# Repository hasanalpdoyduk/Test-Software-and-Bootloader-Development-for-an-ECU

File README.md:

# Test Software and Bootloader Development for an ECU

A bootloader has been developed that enables firmware updates without external programmers. The system runs on a 16-bit dsPIC33 microcontroller and supports CAN and UART interfaces.

Software is securely transferred via one of these interfaces and written to the microcontroller's memory using a block-based architecture that ensures data integrity during interrupts. To streamline the update process, a Python-based graphical user interface (GUI) was created for real-time control and monitoring.

Furthermore, a custom board containing the dsPIC33 MCU was designed and manufactured, successfully testing the bootloader and a PWM control implementation.
## Hardware Components

To initially load the bootloader onto the microcontroller or test the PWM control code, an external debugger is required. In this project, Microchip’s **PICkit 5** is used to program the dsPIC33 device.

| Type         | Component                                                        |
| ----------------- | ------------------------------------------------------------------ |
| Microcontroller | [dsPIC33](https://ww1.microchip.com/downloads/aemDocuments/documents/OTH/ProductDocuments/DataSheets/dsPIC33EVXXXGM00X-10X-Family-Data-Sheet-DS70005144H.pdf) |
| CAN Transceiver | [MCP2561](https://ww1.microchip.com/downloads/en/DeviceDoc/20005167C.pdf) |
| LDO              | [LF50](https://www.st.com/resource/en/datasheet/lfxx.pdf) |
| TVS Diode| [SMAJ36CA](https://www.vishay.com/docs/88390/smaj50a.pdf) |
| Schottky Diode| [SS8PH10HM3](https://www.vishay.com/docs/88989/ss8ph10.pdf) |

In addition to main components, other hardware parts such as resistors, capacitors, connectors, and oscillators are listed in the [Bill of Materials (BOM)](https://github.com/hasanalpdoyduk/Test-Software-and-Bootloader-Development-for-an-ECU/blob/main/KiCAD/ECU_SW_Control/Production_Files/BOM/ECU_SW_Control.csv).

## Block Diagram

The fully assembled PCB is shown here: [3D View of PCB](https://github.com/hasanalpdoyduk/Test-Software-and-Bootloader-Development-for-an-ECU/blob/main/Images/3D_view.pdf)

## Tools & Libraries

- KiCad: Used for schematic and PCB design.

- MATLAB Simulink Device Blocks for Microchip: Used to model and generate initial versions of embedded code.

- MPLAB X IDE: Used to compile and flash generated C code to the dsPIC33 MCU.

- Python (PyQt): Used for GUI development to support user interaction and test control.

## Supporting Sources

All technical details and explanations related to the project are available in the [project report](https://github.com/hasanalpdoyduk/Test-Software-and-Bootloader-Development-for-an-ECU/blob/main/Report_Presentation/EE402_Final_Report_AlpDoyduk_S025015_I%CC%87smailAkbas_S024094.pdf). For more in-depth insights or specific inquiries, feel free to reach out via GitHub or refer to the resources listed below.

- [MCC dsPIC33 Bootlader - Video Guide](https://www.youtube.com/watch?v=2LhW11LbNhY): A step-by-step YouTube tutorial demonstrating how to implement a bootloader for dsPIC33 using Microchip Code Configurator (MCC).

- [Microchip Bootloader Library for 16-bit Devices](https://www.microchip.com/en-us/software-library/dspic33-pic24-bootloader): Official documentation and downloadable libraries for implementing bootloaders on 16-bit dsPIC33/PIC24 microcontrollers.

- [16-bit Bootloader Using MCC - Online Course](https://mu.microchip.com/16-bit-bootloaders-using-mcc-device-side): A Microchip University course explaining how to develop a bootloader for dsPIC33 using MCC, covering both theory and practice.
## Authors

- [Hasan Alp Doyduk](https://www.github.com/hasanalpdoyduk)
- [Ismail Akbaş](https://www.github.com/ismailakbas)

Supervised by: Asst. Prof. Umut Başaran

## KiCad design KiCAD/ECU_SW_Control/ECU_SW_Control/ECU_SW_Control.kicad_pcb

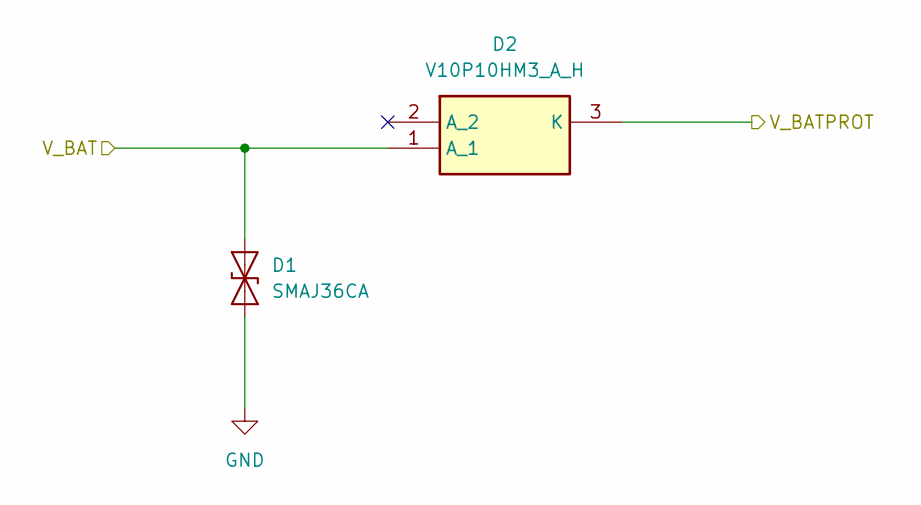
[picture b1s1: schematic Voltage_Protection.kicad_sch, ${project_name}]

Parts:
D1: SMAJ36CA; D_SMA
D2: V10P10HM3_A_H; TO-277A

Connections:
/Connector/V_BAT: D1.1 (A1), D2.1 (A_1); also elsewhere on the board
/LDO/V_BATPROT: D2.3 (K); also elsewhere on the board
GND: D1.2 (A2); also elsewhere on the board

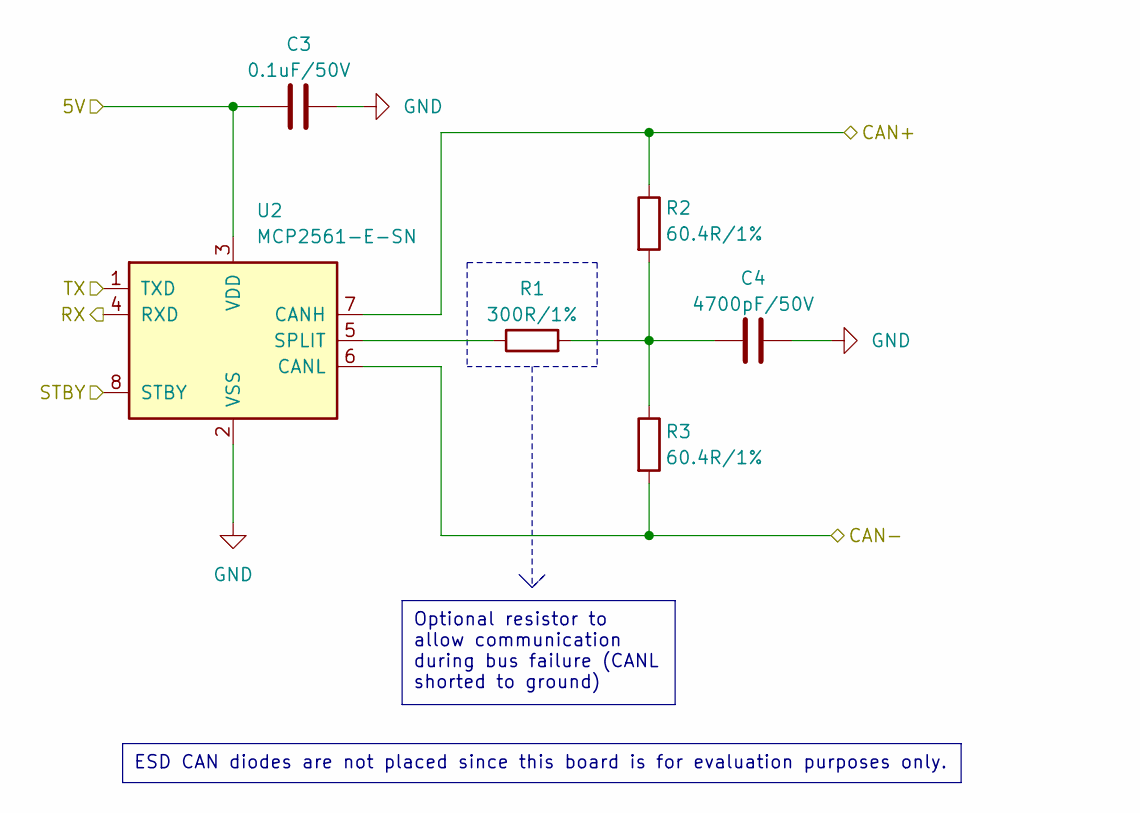
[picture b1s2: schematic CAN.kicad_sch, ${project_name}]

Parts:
C3: 0.1uF/50V; C_0603_1608Metric_Pad1.08x0.95mm_HandSolder; Voltage 50V; Part_Value 0.1uF
C4: 4700pF/50V; C_0603_1608Metric_Pad1.08x0.95mm_HandSolder; Voltage 50V; Part_Value 4700pF
R1: 300R/1%; R_0603_1608Metric_Pad0.98x0.95mm_HandSolder; Tolerance 1%; Part_Value 300R
R2, R3: 60.4R/1%; R_0603_1608Metric_Pad0.98x0.95mm_HandSolder; Tolerance 1%; Part_Value 60.4R
U2: MCP2561-E-SN; SOIC-8_3.9x4.9mm_P1.27mm

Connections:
/CAN/5V: C3.1, U2.3 (VDD); also elsewhere on the board
/CAN/CAN+: R2.1, U2.7 (CANH); also elsewhere on the board
/CAN/CAN-: R3.2, U2.6 (CANL); also elsewhere on the board
/CAN/RX: U2.4 (RXD); also elsewhere on the board
/CAN/STBY: U2.8 (STBY); also elsewhere on the board
/CAN/TX: U2.1 (TXD); also elsewhere on the board
GND: C3.2, C4.2, U2.2 (VSS); also elsewhere on the board
unnamed: C4.1, R1.2, R2.2, R3.1
unnamed: R1.1, U2.5 (SPLIT)

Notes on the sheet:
Optional resistor to allow communication during bus failure (CANL shorted to ground)
ESD CAN diodes are not placed since this board is for evaluation purposes only.

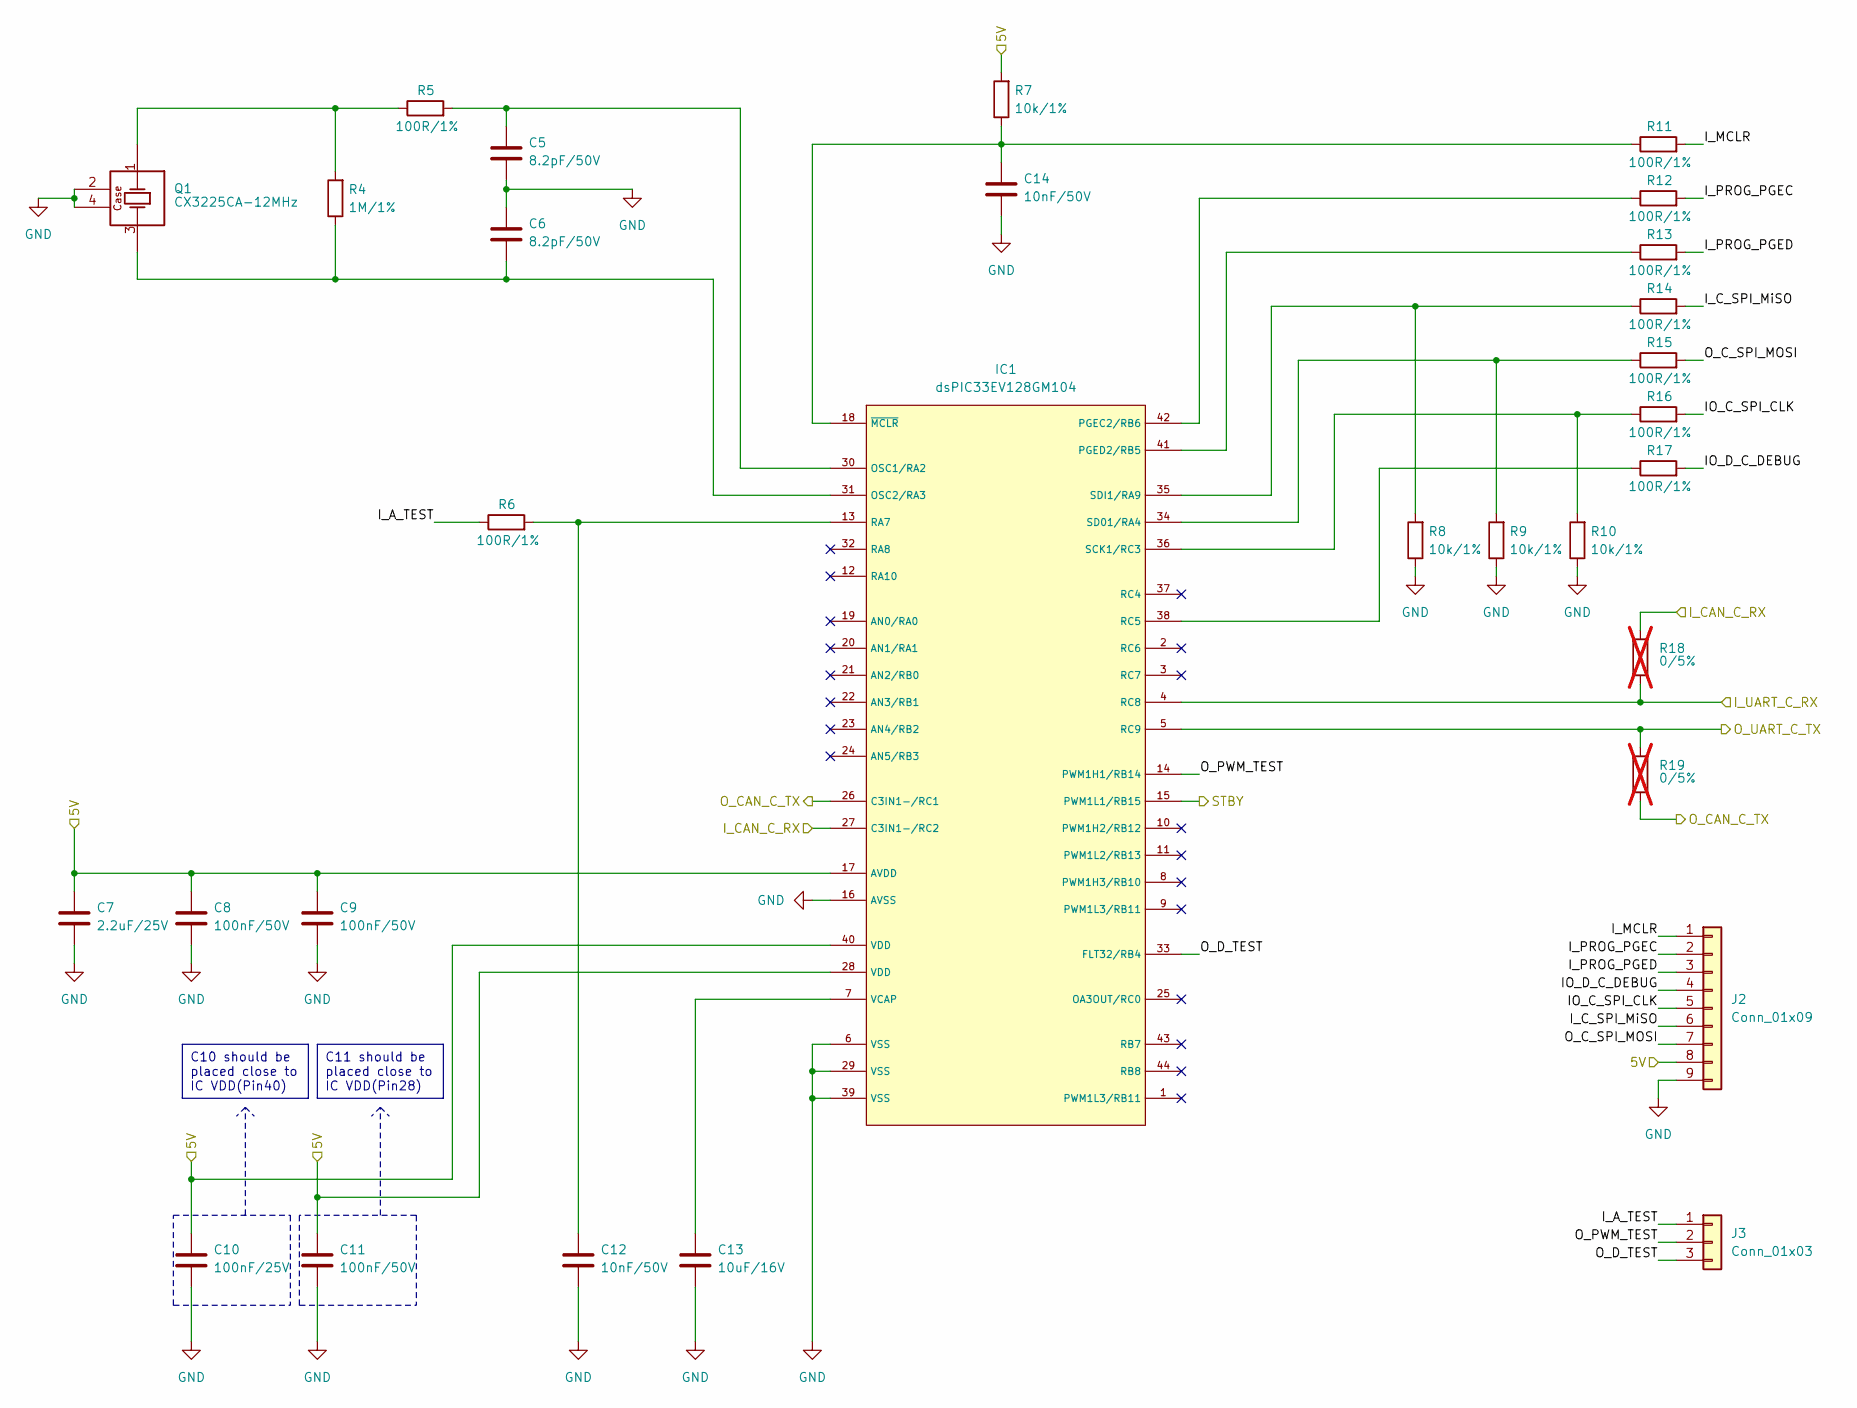
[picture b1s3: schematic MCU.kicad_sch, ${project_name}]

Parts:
C5, C6: 8.2pF/50V; C_0603_1608Metric_Pad1.08x0.95mm_HandSolder; Voltage 50V; Part_Value 8.2pF
C7: 2.2uF/25V; C_0603_1608Metric_Pad1.08x0.95mm_HandSolder; Voltage 25V; Part_Value 2.2uF
C8, C9, C11: 100nF/50V; C_0603_1608Metric_Pad1.08x0.95mm_HandSolder; Voltage 50V; Part_Value 100nF
C10: 100nF/25V; C_0603_1608Metric_Pad1.08x0.95mm_HandSolder; Voltage 25V; Part_Value 100nF
C12, C14: 10nF/50V; C_0603_1608Metric_Pad1.08x0.95mm_HandSolder; Voltage 50V; Part_Value 10nF
C13: 10uF/16V; C_0603_1608Metric_Pad1.08x0.95mm_HandSolder; Voltage 16V; Part_Value 10uF
IC1: dsPIC33EV128GM104; TQFP-44_10x10mm_P0.8mm
J2: Conn_01x09; PinHeader_1x09_P2.54mm_Vertical
J3: Conn_01x03; PinHeader_1x03_P2.54mm_Vertical
Q1: CX3225CA-12MHz; CX3225SB40000D0FLJCC
R4: 1M/1%; R_0603_1608Metric_Pad0.98x0.95mm_HandSolder; Tolerance 1%; Part_Value 1M
R5, R6, R11, R12, R13, R14, R15, R16, R17: 100R/1%; R_0603_1608Metric_Pad0.98x0.95mm_HandSolder; Tolerance 1%; Part_Value 100R
R7, R8, R9, R10: 10k/1%; R_0603_1608Metric_Pad0.98x0.95mm_HandSolder; Tolerance 1%; Part_Value 10k
R18, R19: 0/5%; R_0603_1608Metric_Pad0.98x0.95mm_HandSolder; Tolerance 5%; Part_Value 0; not fitted

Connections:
/CAN/5V: C7.1, C8.1, C9.1, C10.1, C11.1, IC1.17 (AVDD), IC1.28 (VDD), IC1.40 (VDD), J2.8, R7.2; also elsewhere on the board
/CAN/RX: IC1.27 (C3IN1-/RC2), R18.1; also elsewhere on the board
/CAN/STBY: IC1.15 (PWM1L1/RB15); also elsewhere on the board
/CAN/TX: IC1.26 (C3IN1-/RC1), R19.2; also elsewhere on the board
/Connector/COMM1: IC1.5 (RC9), R19.1; also elsewhere on the board
/Connector/COMM2: IC1.4 (RC8), R18.2; also elsewhere on the board
/MCU/IO_C_SPI_CLK: J2.5, R16.2
/MCU/IO_D_C_DEBUG: J2.4, R17.2
/MCU/I_A_TEST: J3.1, R6.1
/MCU/I_C_SPI_MiSO: J2.6, R14.2
/MCU/I_MCLR: J2.1, R11.2
/MCU/I_PROG_PGEC: J2.2, R12.2
/MCU/I_PROG_PGED: J2.3, R13.2
/MCU/O_C_SPI_MOSI: J2.7, R15.2
/MCU/O_D_TEST: IC1.33 (FLT32/RB4), J3.3
/MCU/O_PWM_TEST: IC1.14 (PWM1H1/RB14), J3.2
GND: C5.2, C6.1, C7.2, C8.2, C9.2, C10.2, C11.2, C12.2, C13.2, C14.2, IC1.6 (VSS), IC1.16 (AVSS), IC1.29 (VSS), IC1.39 (VSS), J2.9, Q1.2 (GND), Q1.4 (GND), R8.1, R9.1, R10.1; also elsewhere on the board
unnamed: C5.1, IC1.30 (OSC1/RA2), R5.2
unnamed: C6.2, IC1.31 (OSC2/RA3), Q1.3 (OSC2), R4.1
unnamed: IC1.42 (PGEC2/RB6), R12.1
unnamed: IC1.41 (PGED2/RB5), R13.1
unnamed: C12.1, IC1.13 (RA7), R6.2
unnamed: IC1.38 (RC5), R17.1
unnamed: IC1.36 (SCK1/RC3), R10.2, R16.1
unnamed: IC1.34 (SD01/RA4), R9.2, R15.1
unnamed: IC1.35 (SDI1/RA9), R8.2, R14.1
unnamed: C13.1, IC1.7 (VCAP)
unnamed: C14.1, IC1.18 (~MCLR), R7.1, R11.1
unnamed: Q1.1 (OSC1), R4.2, R5.1

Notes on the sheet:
C11 should be placed close to IC VDD(Pin28)
C10 should be placed close to IC VDD(Pin40)

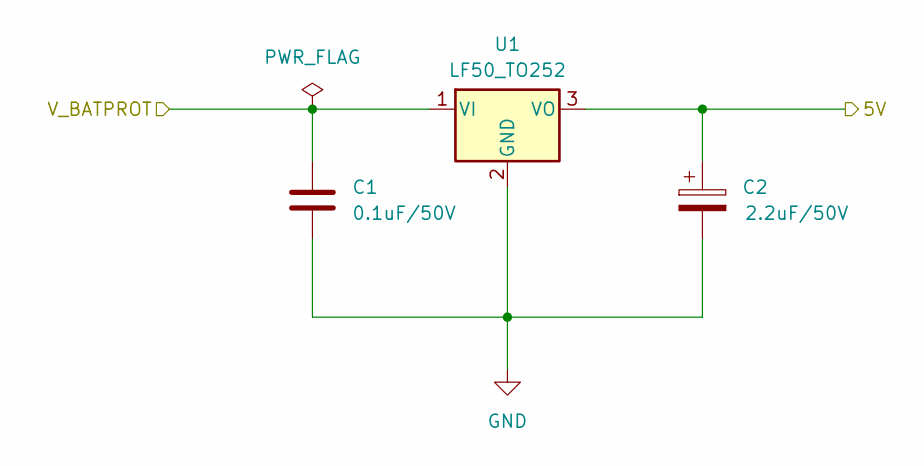
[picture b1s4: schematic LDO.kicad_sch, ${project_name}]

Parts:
C1: 0.1uF/50V; C_0603_1608Metric_Pad1.08x0.95mm_HandSolder; Voltage 50V; Part_Value 0.1uF
C2: 2.2uF/50V; CP_Elec_4x5.3; Voltage 50V; Part_Value 2.2uF
U1: LF50_TO252; LF50CDTTRY

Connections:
/CAN/5V: C2.1, U1.3 (VO); also elsewhere on the board
/LDO/V_BATPROT: C1.1, U1.1 (VI); also elsewhere on the board
GND: C1.2, C2.2, U1.2 (GND); also elsewhere on the board

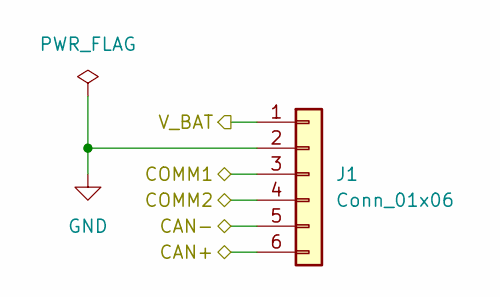
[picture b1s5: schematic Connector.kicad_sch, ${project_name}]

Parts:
J1: Conn_01x06; PinHeader_1x06_P2.54mm_Vertical

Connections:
/CAN/CAN+: J1.6; also elsewhere on the board
/CAN/CAN-: J1.5; also elsewhere on the board
/Connector/COMM1: J1.3; also elsewhere on the board
/Connector/COMM2: J1.4; also elsewhere on the board
/Connector/V_BAT: J1.1; also elsewhere on the board
GND: J1.2; also elsewhere on the board

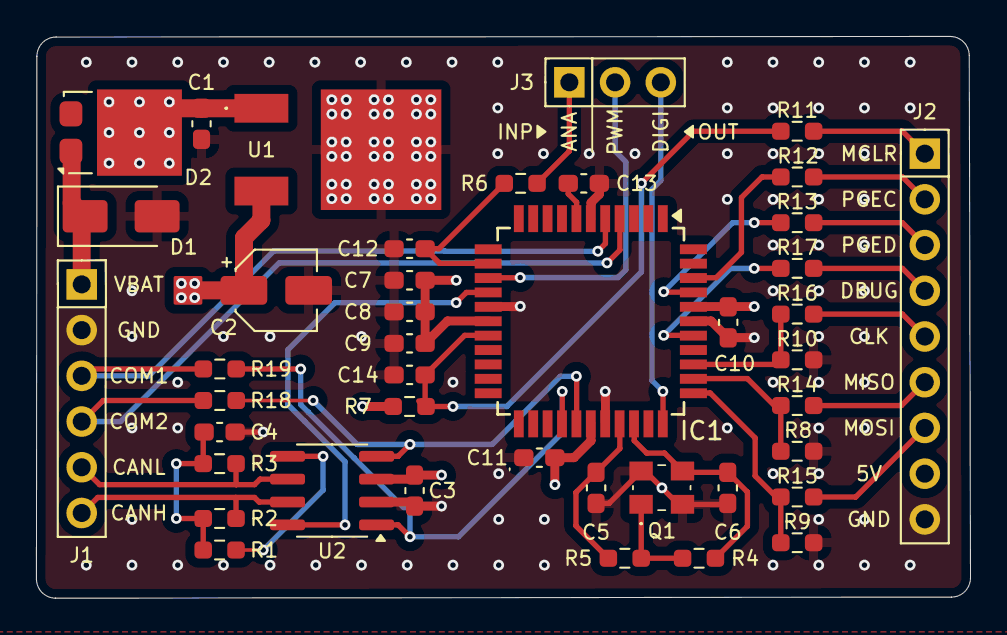
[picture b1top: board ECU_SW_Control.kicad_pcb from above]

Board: 4 copper layers, 51.9 x 31.2 mm, 42 parts (0 on the bottom side), 35 nets.

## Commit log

2025-08-01 Initial commit with all files
